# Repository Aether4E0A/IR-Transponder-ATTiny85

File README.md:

# IR-Transponder-ATTiny85

This Repository is for the open source, open hardware IR Transponder, using the ATTiny85.

These are files for usage in KiCad, an open source PCB design software.

To order boards, submit the .kicad_pcb file to a manufacturer, such as OSHPark.com.

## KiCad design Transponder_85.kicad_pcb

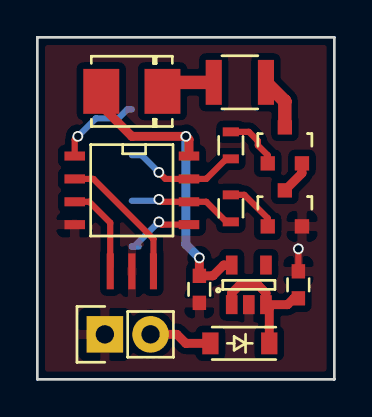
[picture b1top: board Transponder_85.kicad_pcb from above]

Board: 2 copper layers, 16.5 x 19.0 mm, 14 parts (1 on the bottom side), 15 nets.

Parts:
C1, C2: .1u; C_0603
D1: LED; DO-214BA
D2: D; SOD-123
IC1: ATTINY85-S; SOIC-8-N
P1: CONN_01X02; Pin_Header_Straight_1x02
P2: CONN_01X04; conn4
Q1, Q2: BSS138; SOT-23
R1, R2: R; R_0603
R3: R; R_1210
U1: APE8865Y5-33-HF-3; SOT-23-5
X1: CRYSTAL_SMD; myResonator

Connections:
+5V: C2.1, D1.2, IC1.8, U1.5
GND: C1.2, C2.2, IC1.4, P1.1, Q2.2, U1.2, X1.3
unnamed: C1.1, D2.1, U1.1, U1.3
unnamed: D1.1, R3.1
unnamed: D2.2, P1.2
unnamed: IC1.2, X1.1
unnamed: IC1.3, X1.2
unnamed: Q1.1, R1.1
unnamed: Q1.2, Q2.3
unnamed: Q1.3, R3.2
unnamed: Q2.1, R2.2
PB0: IC1.5, P2.4
PB1: IC1.6, P2.3, R2.1
PB2: IC1.7, P2.2, R1.2
PB5: IC1.1, P2.1
